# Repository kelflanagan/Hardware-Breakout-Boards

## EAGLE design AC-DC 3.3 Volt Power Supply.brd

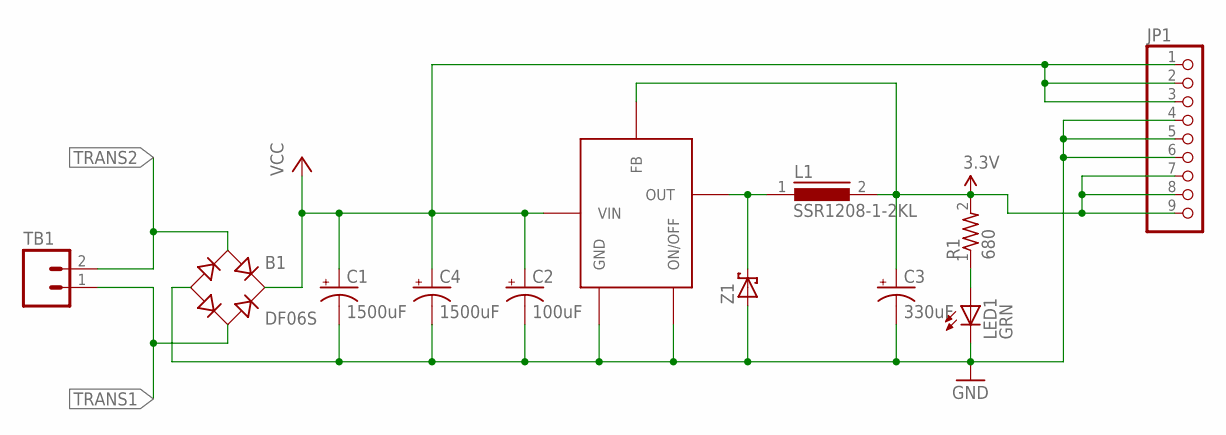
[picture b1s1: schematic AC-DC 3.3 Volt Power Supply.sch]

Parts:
B1: DF06S; DFS
C1, C4: 1500uF; CAP_J16
C2: 100uF; CAP_F
C3: 330uF; CAP_F
JP1: PINHD-1X9; 1X09
L1: SSR1208-1-2KL; DR125
LED1: GRN; CHIP-LED0603
R1: 680; 0603_RESISTOR
REG1: TL2575; TO-263-6
TB1: TERMINAL_BLOCK_2; TERMINL_BLOCK_2_POS
Z1: SCHOTTKY_DIODE; DIODE_SMB

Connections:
3.3V: C3.+, JP1.7, JP1.8, JP1.9, L1.2, R1.2, REG1.4 (FB)
GND: B1.-, C1.1 (-), C2.-, C3.-, C4.1 (-), JP1.4, JP1.5, JP1.6, LED1.C, REG1.3 (GND), REG1.5 (ON/OFF), Z1.A
unnamed: LED1.A, R1.1
unnamed: L1.1, REG1.2 (OUT), Z1.C
TRANS1: B1.AC2, TB1.1
TRANS2: B1.AC1, TB1.2
VCC: B1.+, C1.2 (+), C2.+, C4.2 (+), JP1.1, JP1.2, JP1.3, REG1.1 (VIN)

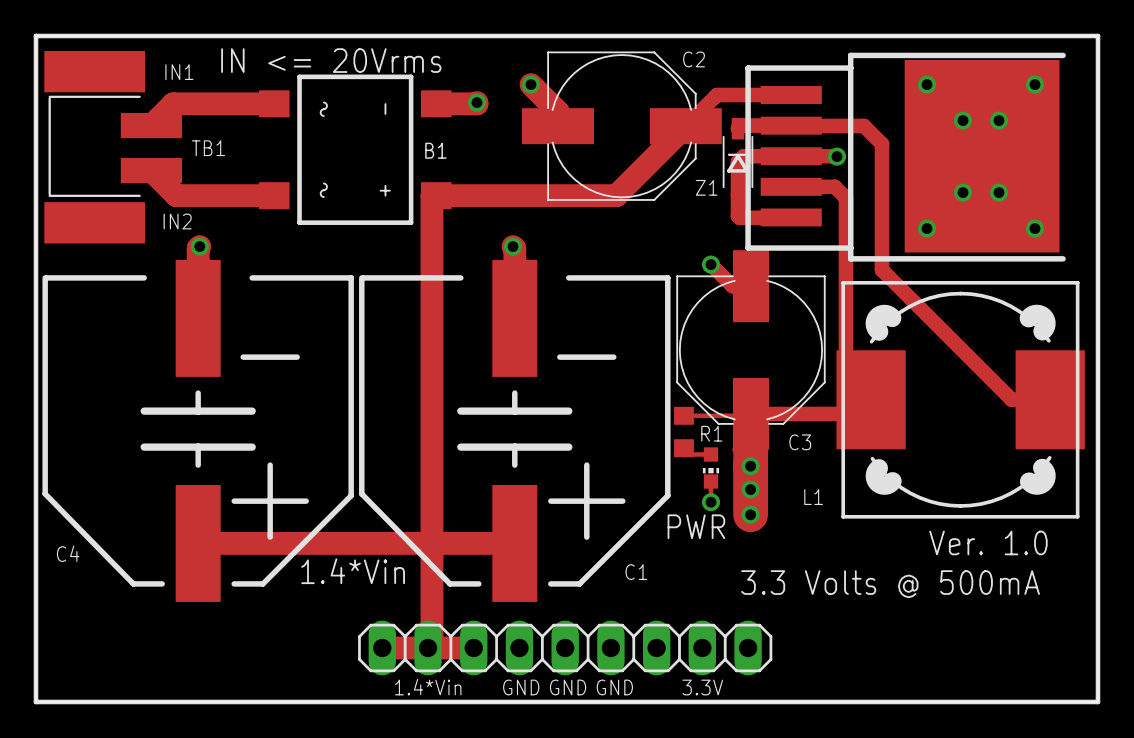
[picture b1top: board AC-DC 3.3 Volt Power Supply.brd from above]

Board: 4 copper layers, 59.0 x 37.0 mm, 12 parts (0 on the bottom side), 7 nets.

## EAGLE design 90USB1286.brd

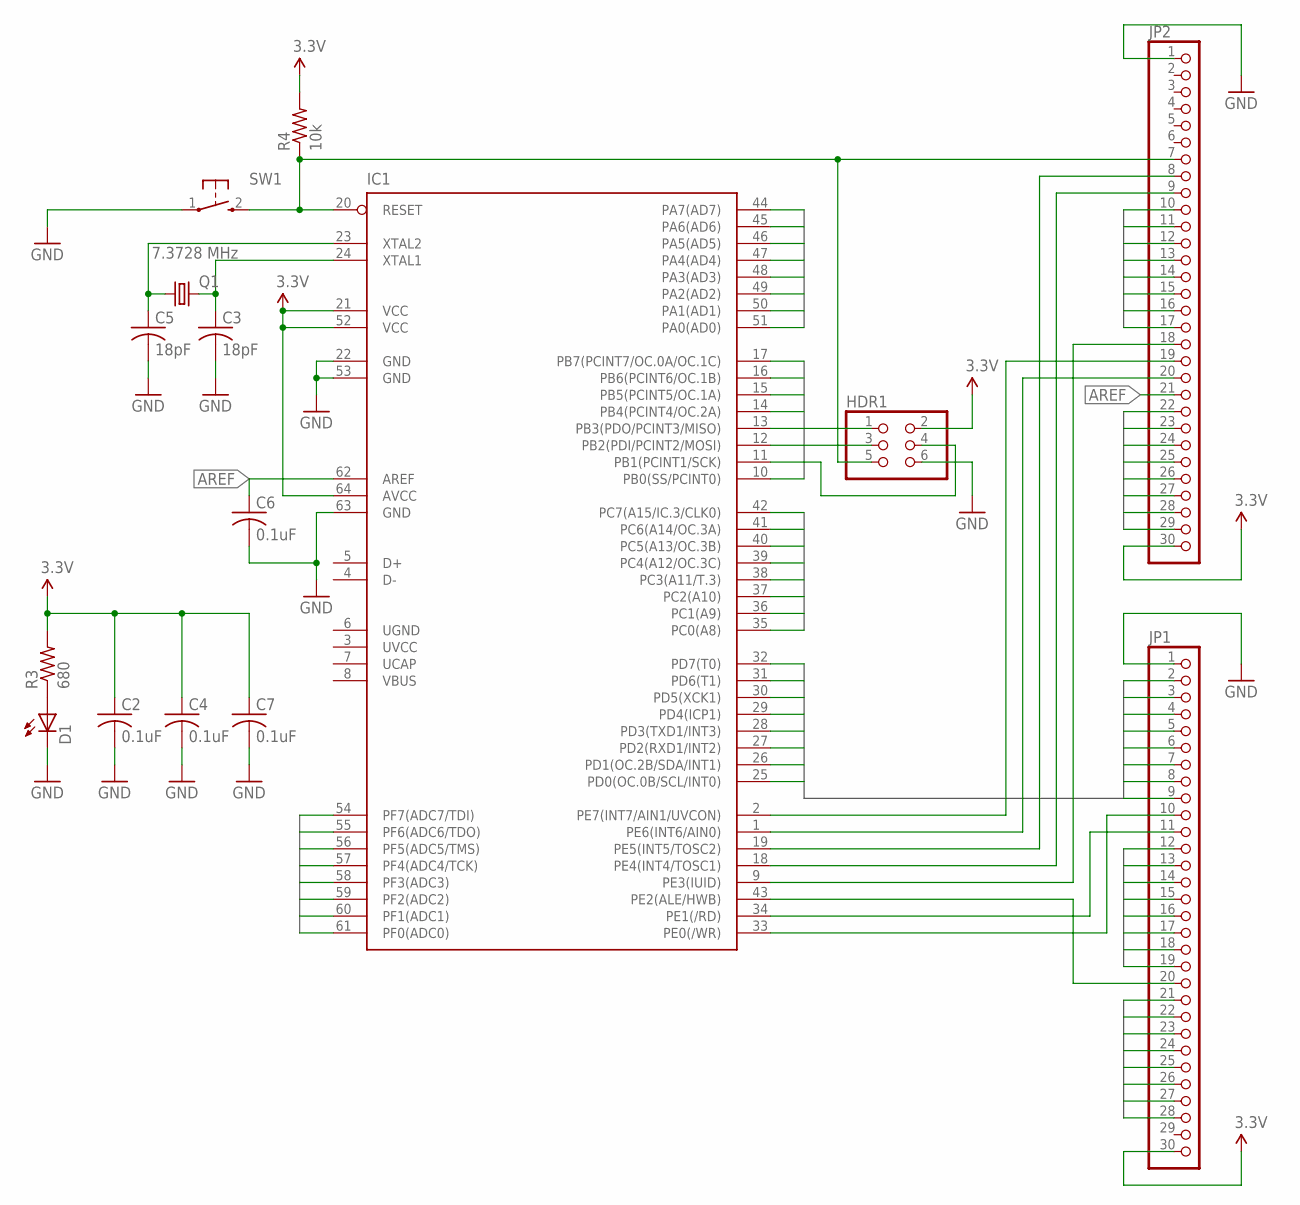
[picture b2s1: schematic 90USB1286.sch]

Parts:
C2, C4, C6, C7: 0.1uF; 0603_RESISTOR
C3, C5: 18pF; 0603_RESISTOR
D1: LEDCHIP-LED0603; CHIP-LED0603
HDR1: HEADER_2X3
IC1: AT90USB1286MLF; MLF64
JP1, JP2: PINHD-1X30; 1X30
Q1: 7.3728 MHz; CTS406
R3: 680; 0603_RESISTOR
R4: 10k; 0603_RESISTOR
SW1: TAC-SWITCH

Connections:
3.3V: C2.1, C4.1, C7.1, HDR1.2, IC1.21 (VCC), IC1.52 (VCC), IC1.64 (AVCC), JP1.30, JP2.30, R3.2, R4.2
A0: IC1.51 (PA0(AD0)), JP1.28
A1: IC1.50 (PA1(AD1)), JP1.27
A2: IC1.49 (PA2(AD2)), JP1.26
A3: IC1.48 (PA3(AD3)), JP1.25
A4: IC1.47 (PA4(AD4)), JP1.24
A5: IC1.46 (PA5(AD5)), JP1.23
A6: IC1.45 (PA6(AD6)), JP1.22
A7: IC1.44 (PA7(AD7)), JP1.21
AREF: C6.1, IC1.62 (AREF), JP2.21
B0: IC1.10 (PB0(SS/PCINT0)), JP2.17
B1: HDR1.3, IC1.11 (PB1(PCINT1/SCK)), JP2.16
B2: HDR1.4, IC1.12 (PB2(PDI/PCINT2/MOSI)), JP2.15
B3: HDR1.1, IC1.13 (PB3(PDO/PCINT3/MISO)), JP2.14
B4: IC1.14 (PB4(PCINT4/OC.2A)), JP2.13
B5: IC1.15 (PB5(PCINT5/OC.1A)), JP2.12
B6: IC1.16 (PB6(PCINT6/OC.1B)), JP2.11
B7: IC1.17 (PB7(PCINT7/OC.0A/OC.1C)), JP2.10
C0: IC1.35 (PC0(A8)), JP1.12
C1: IC1.36 (PC1(A9)), JP1.13
C2: IC1.37 (PC2(A10)), JP1.14
C3: IC1.38 (PC3(A11/T.3)), JP1.15
C4: IC1.39 (PC4(A12/OC.3C)), JP1.16
C5: IC1.40 (PC5(A13/OC.3B)), JP1.17
C6: IC1.41 (PC6(A14/OC.3A)), JP1.18
C7: IC1.42 (PC7(A15/IC.3/CLK0)), JP1.19
D0: IC1.25 (PD0(OC.0B/SCL/INT0)), JP1.2
D1: IC1.26 (PD1(OC.2B/SDA/INT1)), JP1.3
D2: IC1.27 (PD2(RXD1/INT2)), JP1.4
D3: IC1.28 (PD3(TXD1/INT3)), JP1.5
D4: IC1.29 (PD4(ICP1)), JP1.6
D5: IC1.30 (PD5(XCK1)), JP1.7
D6: IC1.31 (PD6(T1)), JP1.8
D7: IC1.32 (PD7(T0)), JP1.9
E0: IC1.33 (PE0(/WR)), JP1.10
E1: IC1.34 (PE1(/RD)), JP1.11
E2: IC1.43 (PE2(ALE/HWB)), JP1.20
E3: IC1.9 (PE3(IUID)), JP2.18
E4: IC1.18 (PE4(INT4/TOSC1)), JP2.9
E5: IC1.19 (PE5(INT5/TOSC2)), JP2.8
E6: IC1.1 (PE6(INT6/AIN0)), JP2.20
E7: IC1.2 (PE7(INT7/AIN1/UVCON)), JP2.19
F0: IC1.61 (PF0(ADC0)), JP2.22
F1: IC1.60 (PF1(ADC1)), JP2.23
F2: IC1.59 (PF2(ADC2)), JP2.24
F3: IC1.58 (PF3(ADC3)), JP2.25
F4: IC1.57 (PF4(ADC4/TCK)), JP2.26
F5: IC1.56 (PF5(ADC5/TMS)), JP2.27
F6: IC1.55 (PF6(ADC6/TDO)), JP2.28
F7: IC1.54 (PF7(ADC7/TDI)), JP2.29
GND: C2.2, C3.2, C4.2, C5.2, C6.2, C7.2, D1.C, HDR1.6, IC1.22 (GND), IC1.53 (GND), IC1.63 (GND), JP1.1, JP2.1, SW1.1
unnamed: C5.1, IC1.23 (XTAL2), Q1.1
unnamed: C3.1, IC1.24 (XTAL1), Q1.3 (2)
unnamed: D1.A, R3.1
RESET: HDR1.5, IC1.20 (RESET), JP2.7, R4.1, SW1.2
UCAP: IC1.7 (UCAP)
UGND: IC1.6 (UGND)
UVCC: IC1.3 (UVCC)
VBUS: IC1.8 (VBUS)

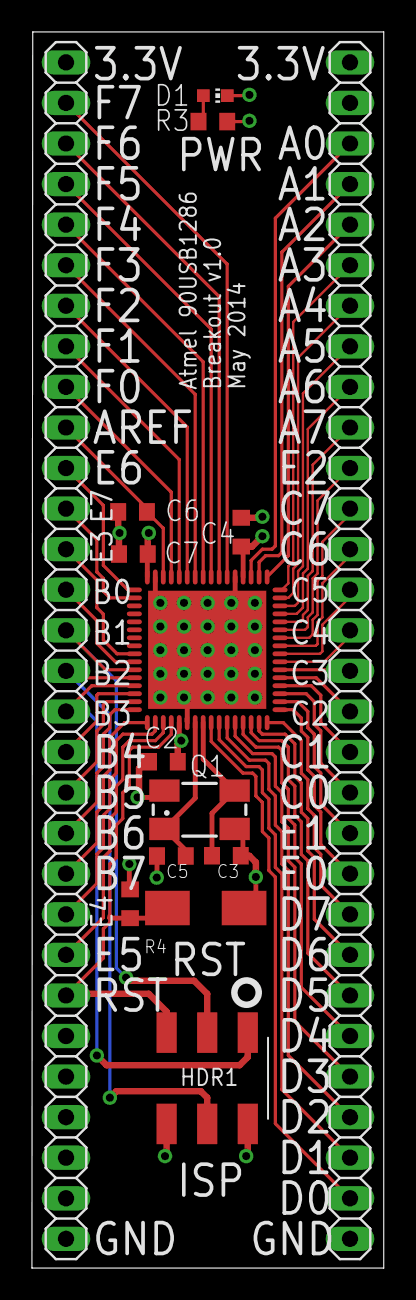
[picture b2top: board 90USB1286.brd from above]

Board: 4 copper layers, 22.0 x 77.4 mm, 15 parts (0 on the bottom side), 55 nets.

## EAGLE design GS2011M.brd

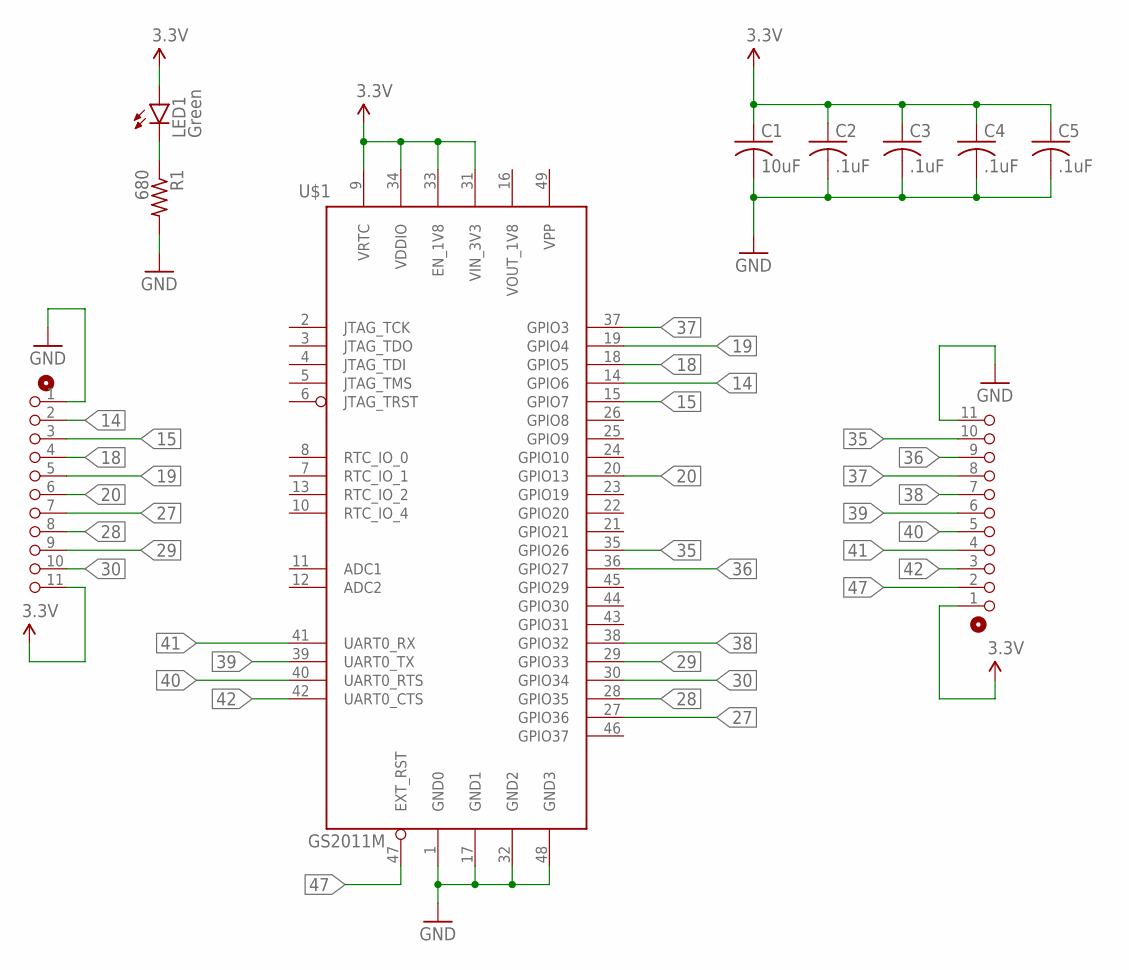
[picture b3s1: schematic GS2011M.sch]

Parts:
C1: 10uF; 0603_CAP
C2, C3, C4, C5: .1uF; 0603_CAP
LED1: Green; 0603_LED
P1, P2: PIN-11X1
R1: 680; 0603_RESISTOR
U$1: GS2011M

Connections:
3.3V: C1.1, C2.1, C3.1, C4.1, C5.1, LED1.A, P1.11, P2.1, U$1.9 (VRTC), U$1.31 (VIN_3V3), U$1.33 (EN_1V8), U$1.34 (VDDIO)
14: P1.2, U$1.14 (GPIO6)
15: P1.3, U$1.15 (GPIO7)
18: P1.4, U$1.18 (GPIO5)
19: P1.5, U$1.19 (GPIO4)
20: P1.6, U$1.20 (GPIO13)
27: P1.7, U$1.27 (GPIO36)
28: P1.8, U$1.28 (GPIO35)
29: P1.9, U$1.29 (GPIO33)
30: P1.10, U$1.30 (GPIO34)
35: P2.10, U$1.35 (GPIO26)
36: P2.9, U$1.36 (GPIO27)
37: P2.8, U$1.37 (GPIO3)
38: P2.7, U$1.38 (GPIO32)
39: P2.6, U$1.39 (UART0_TX)
40: P2.5, U$1.40 (UART0_RTS)
41: P2.4, U$1.41 (UART0_RX)
42: P2.3, U$1.42 (UART0_CTS)
47: P2.2, U$1.47 (EXT_RST)
GND: C1.2, C2.2, C3.2, C4.2, C5.2, P1.1, P2.11, R1.2, U$1.1 (GND0), U$1.17 (GND1), U$1.32 (GND2), U$1.48 (GND3)
unnamed: LED1.C, R1.1
VOUT_1V8: U$1.16 (VOUT_1V8)

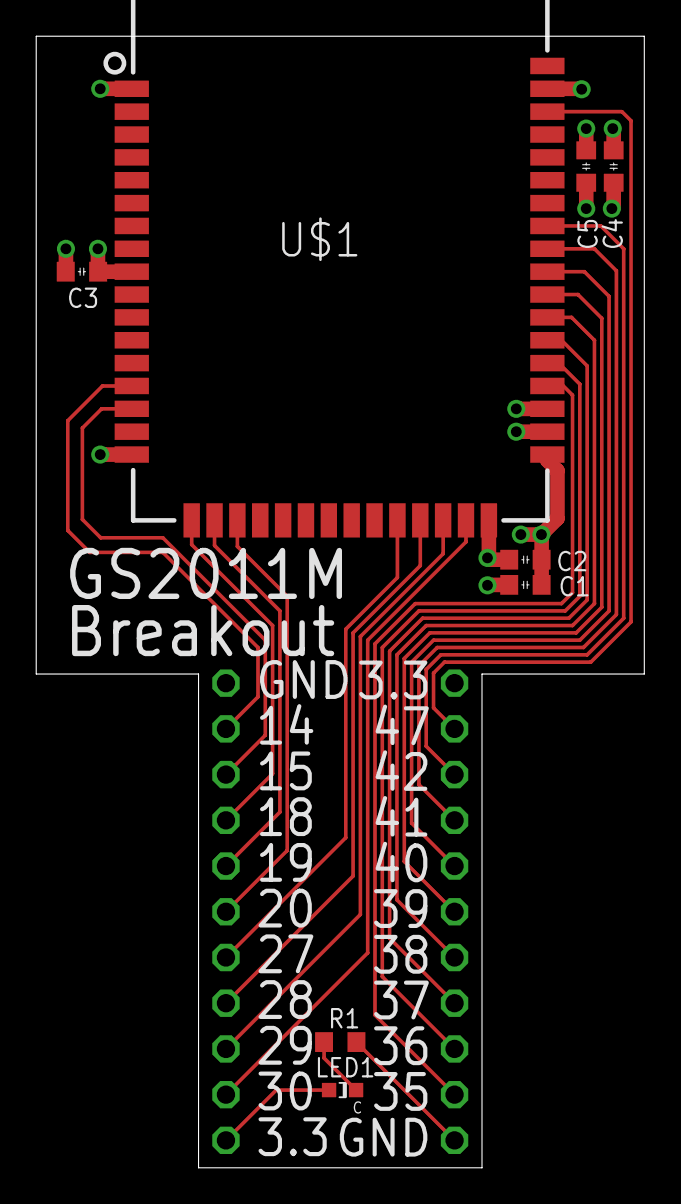
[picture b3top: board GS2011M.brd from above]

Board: 4 copper layers, 33.8 x 62.9 mm, 10 parts (0 on the bottom side), 21 nets.

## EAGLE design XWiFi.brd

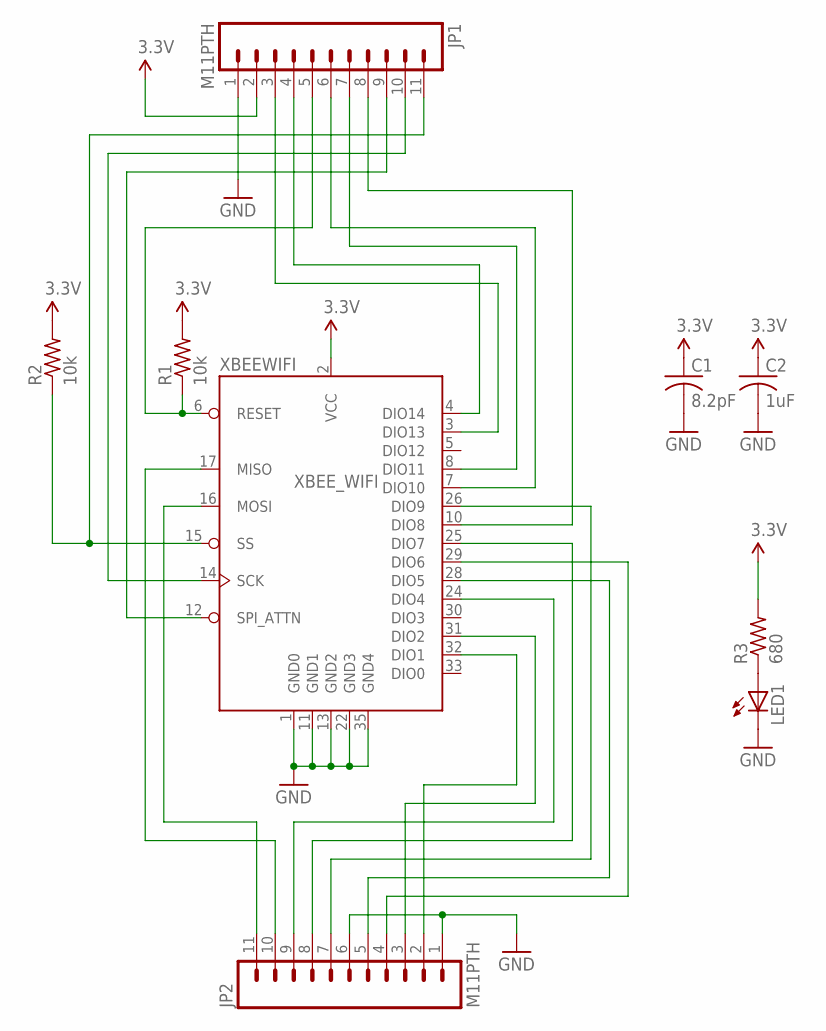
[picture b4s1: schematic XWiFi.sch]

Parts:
C1: 8.2pF; 0603_RESISTOR
C2: 1uF; 0603_RESISTOR
JP1, JP2: M11PTH; 1X11
LED1: LEDCHIP-LED0603; CHIP-LED0603
R1, R2: 10k; 0603_RESISTOR
R3: 680; 0603_RESISTOR
XBEEWIFI: XBEE_WIFI

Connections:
3.3V: C1.1, C2.1, JP1.2, R1.2, R2.2, R3.2, XBEEWIFI.2 (VCC)
GND: C1.2, C2.2, JP1.1, JP2.1, JP2.6, LED1.C, XBEEWIFI.1 (GND0), XBEEWIFI.11 (GND1), XBEEWIFI.13 (GND2), XBEEWIFI.22 (GND3), XBEEWIFI.35 (GND4)
unnamed: JP1.5, R1.1, XBEEWIFI.6 (RESET)
unnamed: JP1.11, R2.1, XBEEWIFI.15 (SS)
unnamed: LED1.A, R3.1
unnamed: JP1.3, XBEEWIFI.3 (DIO13)
unnamed: JP1.4, XBEEWIFI.4 (DIO14)
unnamed: JP1.6, XBEEWIFI.7 (DIO10)
unnamed: JP1.7, XBEEWIFI.8 (DIO11)
unnamed: JP2.9, XBEEWIFI.24 (DIO4)
unnamed: JP1.8, XBEEWIFI.10 (DIO8)
unnamed: JP1.9, XBEEWIFI.12 (SPI_ATTN)
unnamed: JP1.10, XBEEWIFI.14 (SCK)
unnamed: JP2.11, XBEEWIFI.16 (MOSI)
unnamed: JP2.3, XBEEWIFI.31 (DIO2)
unnamed: JP2.2, XBEEWIFI.32 (DIO1)
unnamed: JP2.8, XBEEWIFI.25 (DIO7)
unnamed: JP2.7, XBEEWIFI.26 (DIO9)
unnamed: JP2.5, XBEEWIFI.28 (DIO5)
unnamed: JP2.4, XBEEWIFI.29 (DIO6)
unnamed: JP2.10, XBEEWIFI.17 (MISO)

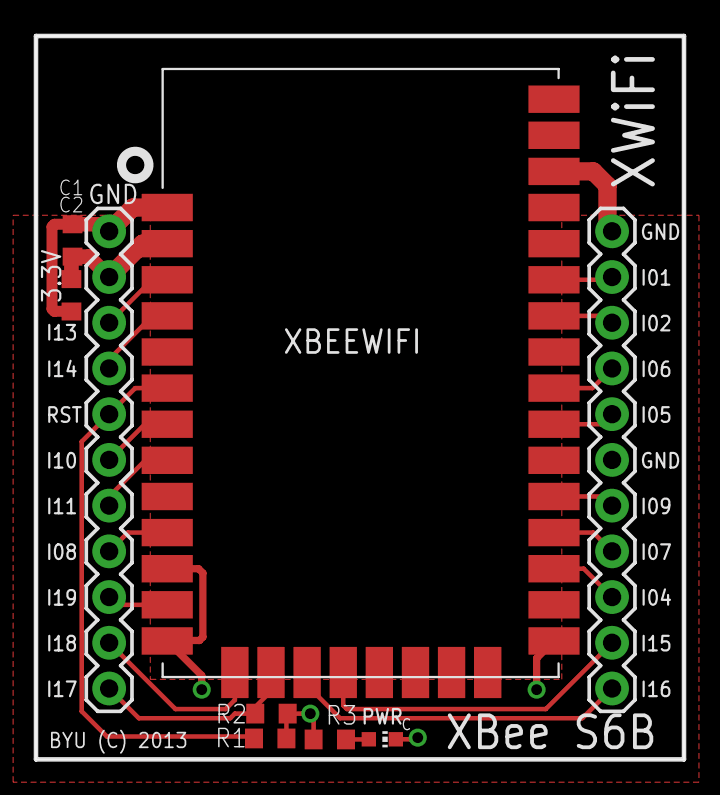
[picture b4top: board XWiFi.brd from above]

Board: 4 copper layers, 36.0 x 40.2 mm, 9 parts (0 on the bottom side), 21 nets.

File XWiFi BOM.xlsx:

Part | Value | Device
C1 | 8.2pF | 0603 Cap
C2 | 1 uF | 0603 Cap
R1 | 10k Ohm | 0603 Resistor
R2 | 10k Ohm | 0603 Resistor
R3 | 680 Ohm | 0603 Resistor
LED1 | Green LED | 0603 LED
Xbee1 | Xbee Wifi Module | Module
HDR1 | 11 pin header | 1x11 header
HDR2 | 11 pin header | 1x11 header

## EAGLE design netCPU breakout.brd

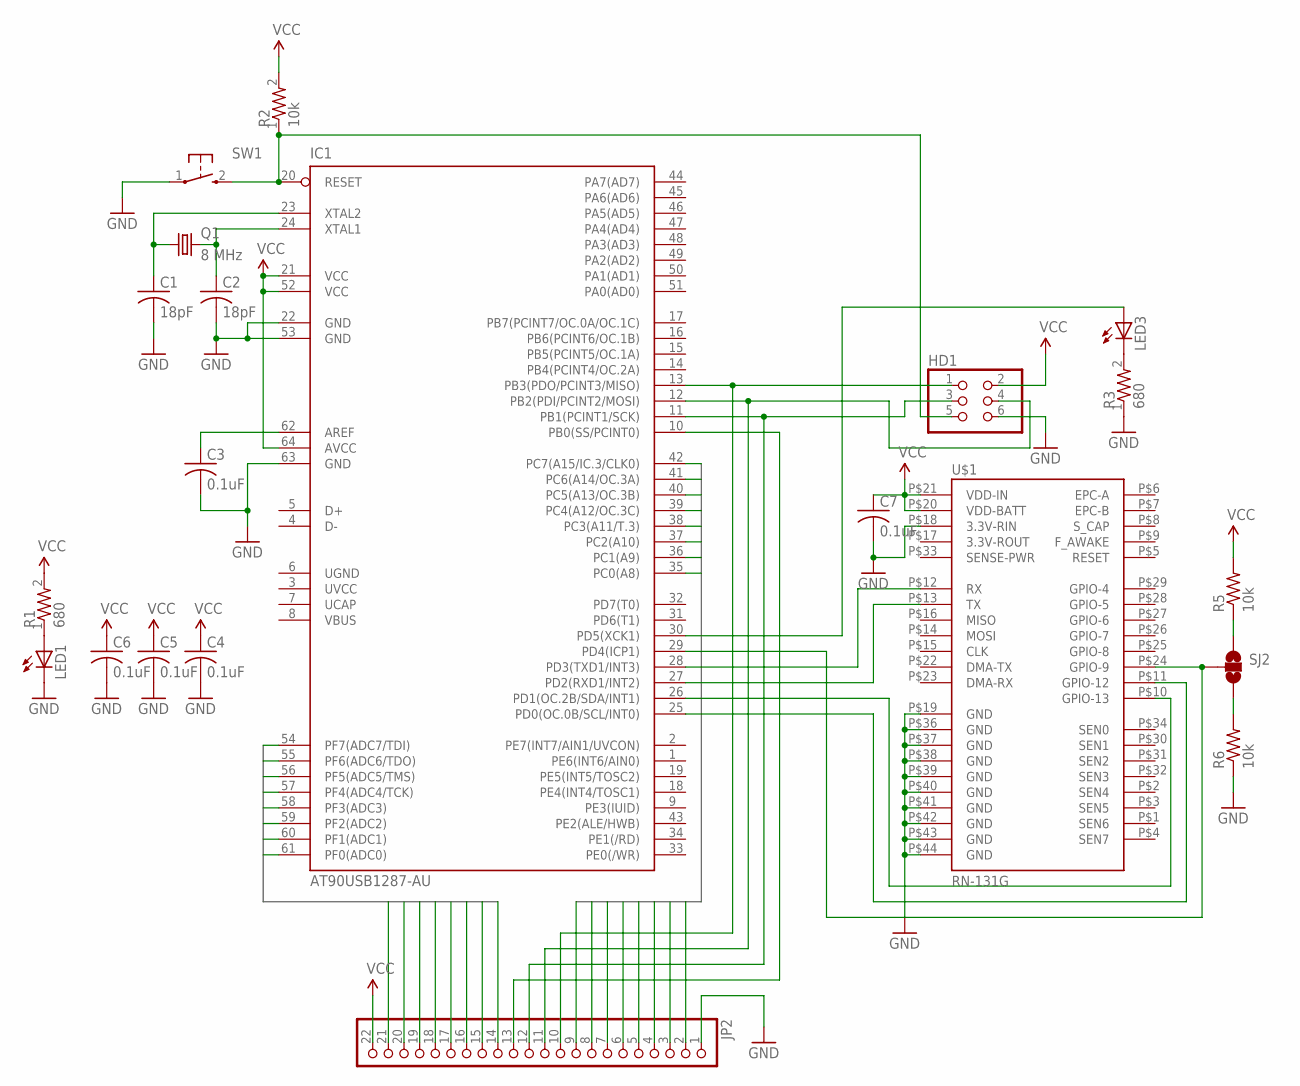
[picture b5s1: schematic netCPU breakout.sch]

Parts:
C1, C2: 18pF; C0603K
C3, C4, C5, C6, C7: 0.1uF; C0603K
HD1: HEADER2X3
IC1: AT90USB1287-AU; TQFP64
JP2: PINHD-1X22; 1X22
LED1, LED3: LEDCHIP-LED0603; CHIP-LED0603
Q1: 8 MHz; HC49UP
R1, R3: 680; 0603_RESISTOR
R2: 10k; 0603_RESISTOR
R5, R6: 10k; R0603
SJ2: SOLDERJUMPER_2WAYPASTE2&3; SJ_3_PASTE2&3
SW1: TAC-SWITCH
U$1: RN-131G

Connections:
GND: C1.2, C2.2, C3.2, C4.2, C5.2, C6.2, C7.2, HD1.6, IC1.22 (GND), IC1.53 (GND), IC1.63 (GND), JP2.1, LED1.C, R3.1, R6.1, SW1.1, U$1.P$18 (3.3V-RIN), U$1.P$19 (GND), U$1.P$36 (GND), U$1.P$37 (GND), U$1.P$38 (GND), U$1.P$39 (GND), U$1.P$40 (GND), U$1.P$41 (GND), U$1.P$42 (GND), U$1.P$43 (GND), U$1.P$44 (GND)
MISO: HD1.1, IC1.13 (PB3(PDO/PCINT3/MISO)), JP2.10
MOSI: HD1.4, IC1.12 (PB2(PDI/PCINT2/MOSI)), JP2.11
unnamed: C1.1, IC1.23 (XTAL2), Q1.1
unnamed: C2.1, IC1.24 (XTAL1), Q1.2
unnamed: LED1.A, R1.1
unnamed: LED3.C, R3.2
unnamed: IC1.28 (PD3(TXD1/INT3)), U$1.P$12 (RX)
unnamed: C3.1, IC1.62 (AREF)
unnamed: IC1.27 (PD2(RXD1/INT2)), U$1.P$13 (TX)
unnamed: IC1.26 (PD1(OC.2B/SDA/INT1)), U$1.P$10 (GPIO-13)
unnamed: IC1.25 (PD0(OC.0B/SCL/INT0)), U$1.P$11 (GPIO-12)
unnamed: IC1.29 (PD4(ICP1)), SJ2.2, U$1.P$24 (GPIO-9)
unnamed: IC1.30 (PD5(XCK1)), LED3.A
unnamed: R6.2, SJ2.3
unnamed: R5.1, SJ2.1
PC0: IC1.35 (PC0(A8)), JP2.2
PC1: IC1.36 (PC1(A9)), JP2.3
PC2: IC1.37 (PC2(A10)), JP2.4
PC3: IC1.38 (PC3(A11/T.3)), JP2.5
PC4: IC1.39 (PC4(A12/OC.3C)), JP2.6
PC5: IC1.40 (PC5(A13/OC.3B)), JP2.7
PC6: IC1.41 (PC6(A14/OC.3A)), JP2.8
PC7: IC1.42 (PC7(A15/IC.3/CLK0)), JP2.9
PF0: IC1.61 (PF0(ADC0)), JP2.14
PF1: IC1.60 (PF1(ADC1)), JP2.15
PF2: IC1.59 (PF2(ADC2)), JP2.16
PF3: IC1.58 (PF3(ADC3)), JP2.17
PF4: IC1.57 (PF4(ADC4/TCK)), JP2.18
PF5: IC1.56 (PF5(ADC5/TMS)), JP2.19
PF6: IC1.55 (PF6(ADC6/TDO)), JP2.20
PF7: IC1.54 (PF7(ADC7/TDI)), JP2.21
RESET: HD1.5, IC1.20 (RESET), R2.1, SW1.2
SCK: HD1.3, IC1.11 (PB1(PCINT1/SCK)), JP2.12
SS: IC1.10 (PB0(SS/PCINT0)), JP2.13
UCAP: IC1.7 (UCAP)
UGND: IC1.6 (UGND)
UVCC: IC1.3 (UVCC)
VBUS: IC1.8 (VBUS)
VCC: C4.1, C5.1, C6.1, C7.1, HD1.2, IC1.21 (VCC), IC1.52 (VCC), IC1.64 (AVCC), JP2.22, R1.2, R2.2, R5.2, U$1.P$20 (VDD-BATT), U$1.P$21 (VDD-IN)

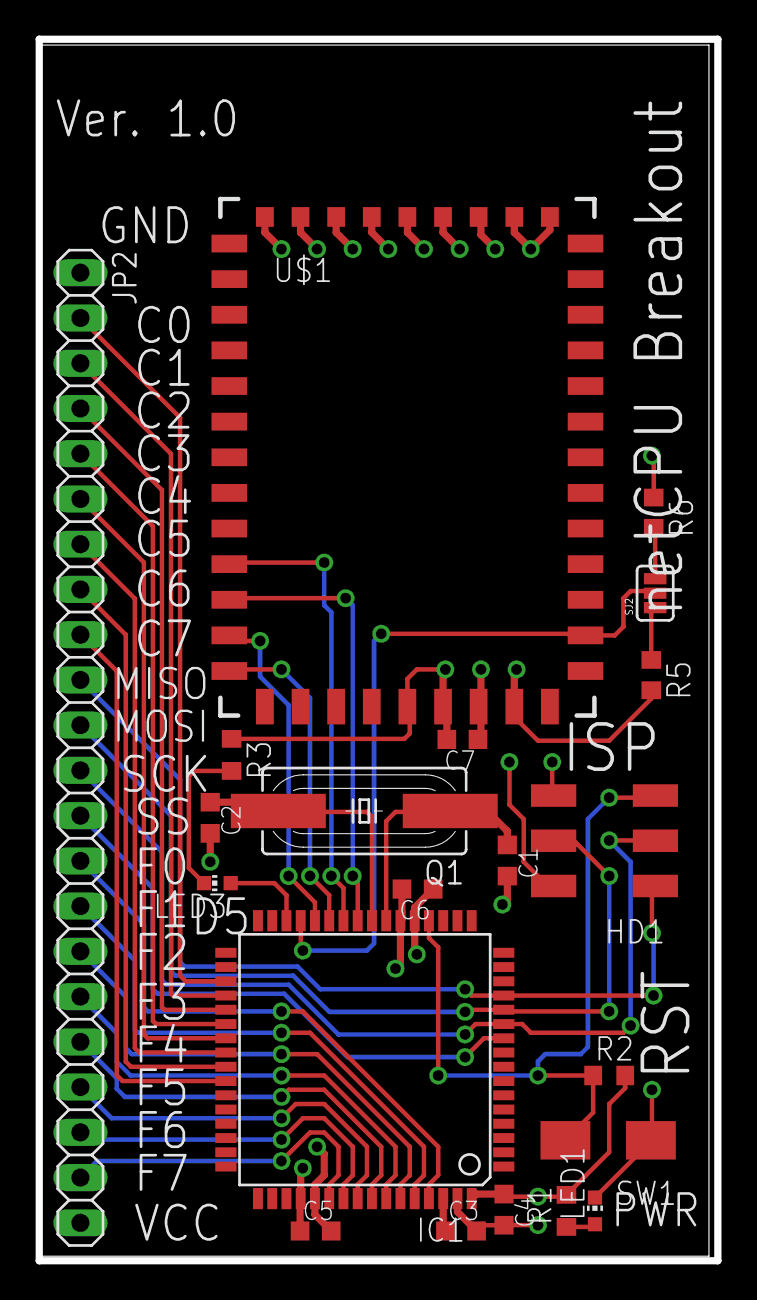
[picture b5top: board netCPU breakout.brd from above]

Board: 4 copper layers, 38.1 x 68.6 mm, 21 parts (0 on the bottom side), 36 nets.

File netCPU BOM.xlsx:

Designation | Description | Size / Value | DigiKey PN | Manufacturer | Unit Price @100 | Reeling Cost | Unit Price
HD1 | Header | 2x3 | 609-3487-6-ND |  | 0.90100000000000002 | 7 | 1.1000000000000001
R1 | Resistor | 680 | P680GDKR-ND | Panasonic | 7.6999999999999999E-2 | 7 | 0.1
R2 | Resistor | 10k | P10KGDKR-ND | Panasonic | 7.6999999999999999E-2 | 7 | 0.1
R3 | Resistor | 680 | P680GDKR-ND | Panasonic | 7.6999999999999999E-2 | 7 | 0.1
R4 | Resistor | 10k | P10KGDKR-ND | Panasonic | 7.6999999999999999E-2 | 7 | 0.1
C1 | Capacitor | 18pF | 399-1052-6-ND | Kemet | 8.5400000000000004E-2 | 7 | 0.1
C2 | Capacitor | 18pF | 399-1052-6-ND | Kemet | 8.5400000000000004E-2 | 7 | 0.1
C3 | Capacitor | 0.1uF | 399-1096-6-ND | Kemet | 7.9899999999999999E-2 | 7 | 0.1
C4 | Capacitor | 0.1uF | 399-1096-6-ND | Kemet | 7.9899999999999999E-2 | 7 | 0.1
C5 | Capacitor | 0.1uF | 399-1096-6-ND | Kemet | 7.9899999999999999E-2 | 7 | 0.1
C6 | Capacitor | 0.1uF | 399-1096-6-ND | Kemet | 7.9899999999999999E-2 | 7 | 0.1
C7 | Capacitor | 0.1uF | 399-1096-6-ND | Kemet | 7.9899999999999999E-2 | 7 | 0.1
Q1 | Crystal | 8MHz | 535-10212-6-ND | ABLS | 0.3175 | 7 | 0.41
SW1 | Tactile Switch | NA | EG4576DKR-ND | E-Switch | 0.62880000000000003 | 7 | 0.77
IC1 | AT90USB1286 | 64TQFP | AT90USB1286-AURCT-ND | Atmel | 10.83 | 0 | 10.83
IC2 | RN-131C | 44 pin Module | 740-1036-ND | MicroChip | 32.39 | 0 | 34.950000000000003
LED1 | Green LED | 0603 | 516-2493-6-ND | Avago | 0.28199999999999997 | 7 | 0.54
LED2 | Green LED | 0603 | 516-2493-6-ND | Avago | 0.28199999999999997 | 7 | 0.54
JP2 | Header | 22x1 | 929400E-01-36-ND | 3M | 0.96799999999999997 |  | 1.28

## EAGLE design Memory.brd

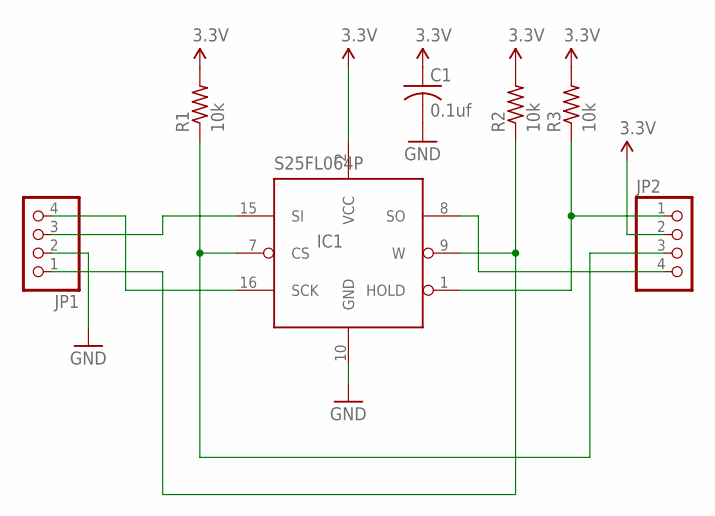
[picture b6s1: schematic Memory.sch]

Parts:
C1: 0.1uf; 0603_CAP
IC1: S25FL064P; SOIC-16
JP1, JP2: PINHD-1X4; 1X04
R1, R2, R3: 10k; 0603_RESISTOR

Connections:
3.3V: C1.1, IC1.2 (VCC), JP2.2, R1.2, R2.2, R3.2
GND: C1.2, IC1.10 (GND), JP1.2
unnamed: IC1.7 (CS), JP2.3, R1.1
unnamed: IC1.9 (W), JP1.1, R2.1
unnamed: IC1.1 (HOLD), JP2.1, R3.1
unnamed: IC1.8 (SO), JP2.4
unnamed: IC1.15 (SI), JP1.3
unnamed: IC1.16 (SCK), JP1.4

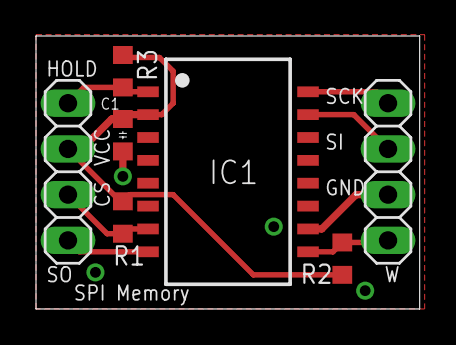
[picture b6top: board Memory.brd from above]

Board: 2 copper layers, 21.3 x 15.2 mm, 7 parts (0 on the bottom side), 8 nets.

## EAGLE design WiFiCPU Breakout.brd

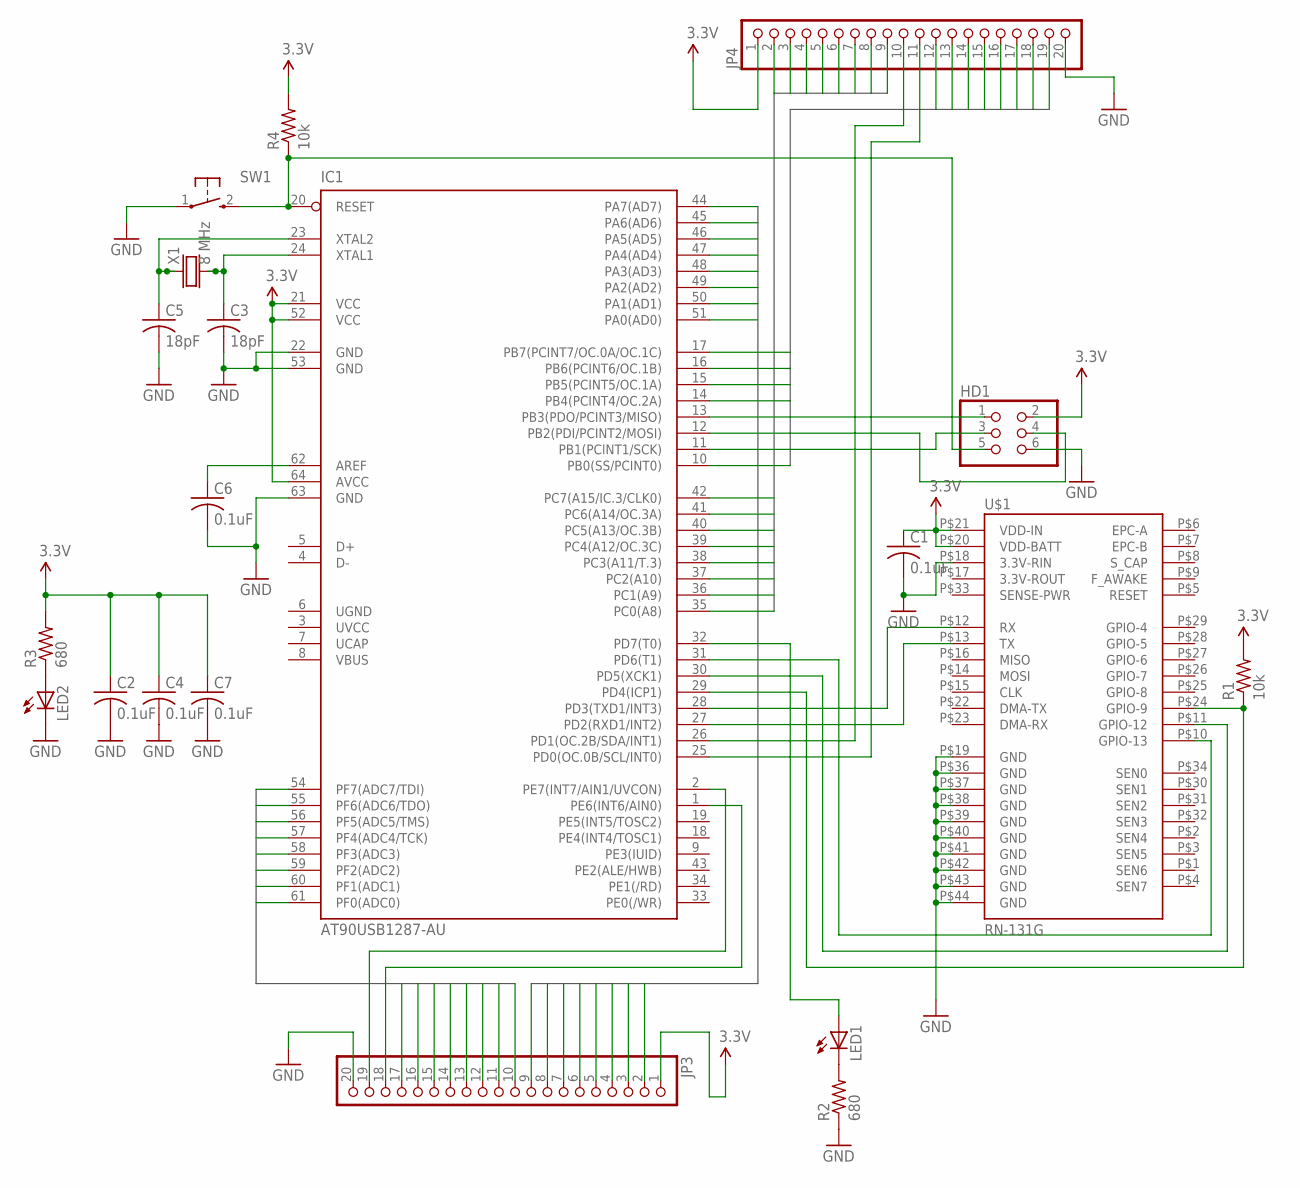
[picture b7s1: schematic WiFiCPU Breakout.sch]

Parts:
C1, C2, C4, C6, C7: 0.1uF; 0603_RESISTOR
C3, C5: 18pF; 0603_RESISTOR
HD1: HEADER2X3
IC1: AT90USB1287-AU; TQFP64
JP3, JP4: PINHD-1X20; 1X20
LED1, LED2: LEDCHIP-LED0603; CHIP-LED0603
R1, R4: 10k; 0603_RESISTOR
R2, R3: 680; 0603_RESISTOR
SW1: TAC-SWITCH
U$1: RN-131G
X1: 8 MHz; CRYSTAL_5X3

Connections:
3.3V: C1.1, C2.1, C4.1, C7.1, HD1.2, IC1.21 (VCC), IC1.52 (VCC), IC1.64 (AVCC), JP3.1, JP4.1, R1.2, R3.2, R4.2, U$1.P$20 (VDD-BATT), U$1.P$21 (VDD-IN)
GND: C1.2, C2.2, C3.2, C4.2, C5.2, C6.2, C7.2, HD1.6, IC1.22 (GND), IC1.53 (GND), IC1.63 (GND), JP3.20, JP4.20, LED2.C, R2.1, SW1.1, U$1.P$18 (3.3V-RIN), U$1.P$19 (GND), U$1.P$36 (GND), U$1.P$37 (GND), U$1.P$38 (GND), U$1.P$39 (GND), U$1.P$40 (GND), U$1.P$41 (GND), U$1.P$42 (GND), U$1.P$43 (GND), U$1.P$44 (GND)
unnamed: C5.1, IC1.23 (XTAL2), X1.1
unnamed: C3.1, IC1.24 (XTAL1), X1.2
unnamed: LED2.A, R3.1
unnamed: LED1.C, R2.2
unnamed: IC1.32 (PD7(T0)), LED1.A
unnamed: IC1.28 (PD3(TXD1/INT3)), U$1.P$12 (RX)
unnamed: C6.1, IC1.62 (AREF)
unnamed: IC1.27 (PD2(RXD1/INT2)), U$1.P$13 (TX)
unnamed: IC1.31 (PD6(T1)), U$1.P$10 (GPIO-13)
unnamed: IC1.30 (PD5(XCK1)), U$1.P$11 (GPIO-12)
unnamed: IC1.29 (PD4(ICP1)), R1.1, U$1.P$24 (GPIO-9)
PA0: IC1.51 (PA0(AD0)), JP3.9
PA1: IC1.50 (PA1(AD1)), JP3.8
PA2: IC1.49 (PA2(AD2)), JP3.7
PA3: IC1.48 (PA3(AD3)), JP3.6
PA4: IC1.47 (PA4(AD4)), JP3.5
PA5: IC1.46 (PA5(AD5)), JP3.4
PA6: IC1.45 (PA6(AD6)), JP3.3
PA7: IC1.44 (PA7(AD7)), JP3.2
PB0: IC1.10 (PB0(SS/PCINT0)), JP4.19
PB1: HD1.3, IC1.11 (PB1(PCINT1/SCK)), JP4.18
PB2: HD1.4, IC1.12 (PB2(PDI/PCINT2/MOSI)), JP4.17
PB3: HD1.1, IC1.13 (PB3(PDO/PCINT3/MISO)), JP4.16
PB4: IC1.14 (PB4(PCINT4/OC.2A)), JP4.15
PB5: IC1.15 (PB5(PCINT5/OC.1A)), JP4.14
PB6: IC1.16 (PB6(PCINT6/OC.1B)), JP4.13
PB7: IC1.17 (PB7(PCINT7/OC.0A/OC.1C)), JP4.12
PC0: IC1.35 (PC0(A8)), JP4.9
PC1: IC1.36 (PC1(A9)), JP4.8
PC2: IC1.37 (PC2(A10)), JP4.7
PC3: IC1.38 (PC3(A11/T.3)), JP4.6
PC4: IC1.39 (PC4(A12/OC.3C)), JP4.5
PC5: IC1.40 (PC5(A13/OC.3B)), JP4.4
PC6: IC1.41 (PC6(A14/OC.3A)), JP4.3
PC7: IC1.42 (PC7(A15/IC.3/CLK0)), JP4.2
PD0: IC1.25 (PD0(OC.0B/SCL/INT0)), JP4.11
PD1: IC1.26 (PD1(OC.2B/SDA/INT1)), JP4.10
PE6: IC1.1 (PE6(INT6/AIN0)), JP3.18
PE7: IC1.2 (PE7(INT7/AIN1/UVCON)), JP3.19
PF0: IC1.61 (PF0(ADC0)), JP3.17
PF1: IC1.60 (PF1(ADC1)), JP3.16
PF2: IC1.59 (PF2(ADC2)), JP3.15
PF3: IC1.58 (PF3(ADC3)), JP3.14
PF4: IC1.57 (PF4(ADC4/TCK)), JP3.13
PF5: IC1.56 (PF5(ADC5/TMS)), JP3.12
PF6: IC1.55 (PF6(ADC6/TDO)), JP3.11
PF7: IC1.54 (PF7(ADC7/TDI)), JP3.10
RESET: HD1.5, IC1.20 (RESET), R4.1, SW1.2
UCAP: IC1.7 (UCAP)
UGND: IC1.6 (UGND)
UVCC: IC1.3 (UVCC)
VBUS: IC1.8 (VBUS)

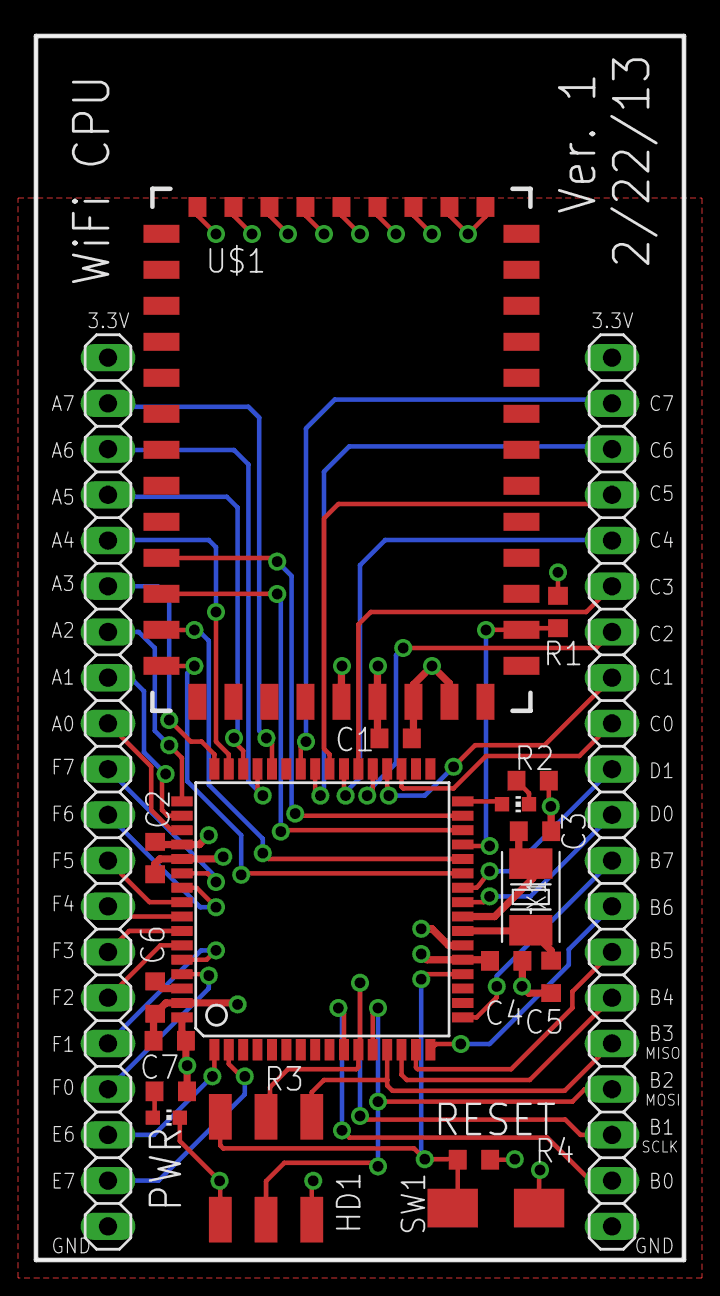
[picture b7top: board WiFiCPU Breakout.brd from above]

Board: 4 copper layers, 36.0 x 68.0 mm, 20 parts (0 on the bottom side), 50 nets.

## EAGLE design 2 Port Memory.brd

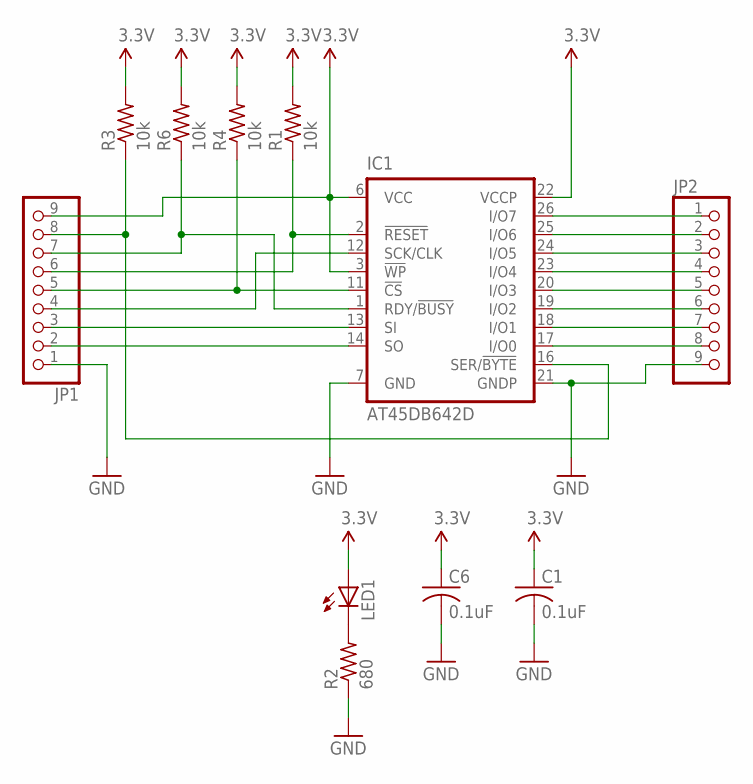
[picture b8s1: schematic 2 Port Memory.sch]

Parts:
C1, C6: 0.1uF; 0603_RESISTOR
IC1: AT45DB642D; 28T-TSOP-1
JP1, JP2: PINHD-1X9; 1X09
LED1: LEDCHIP-LED0603; CHIP-LED0603
R1, R3, R4, R6: 10k; 0603_RESISTOR
R2: 680; 0603_RESISTOR

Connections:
3.3V: C1.1, C6.1, IC1.3 (!WP), IC1.6 (VCC), IC1.22 (VCCP), JP1.9, LED1.A, R1.2, R3.2, R4.2, R6.2
GND: C1.2, C6.2, IC1.7 (GND), IC1.21 (GNDP), JP1.1, JP2.9, R2.1
unnamed: IC1.1 (RDY/!BUSY), JP1.7, R6.1
unnamed: IC1.11 (!CS), JP1.5, R4.1
unnamed: IC1.12 (SCK/CLK), JP1.4
unnamed: LED1.C, R2.2
unnamed: IC1.16 (SER/!BYTE), JP1.8, R3.1
unnamed: IC1.17 (I/O0), JP2.8
unnamed: IC1.18 (I/O1), JP2.7
unnamed: IC1.19 (I/O2), JP2.6
unnamed: IC1.20 (I/O3), JP2.5
unnamed: IC1.23 (I/O4), JP2.4
unnamed: IC1.24 (I/O5), JP2.3
unnamed: IC1.25 (I/O6), JP2.2
unnamed: IC1.26 (I/O7), JP2.1
unnamed: IC1.14 (SO), JP1.2
unnamed: IC1.13 (SI), JP1.3
unnamed: IC1.2 (!RESET), JP1.6, R1.1

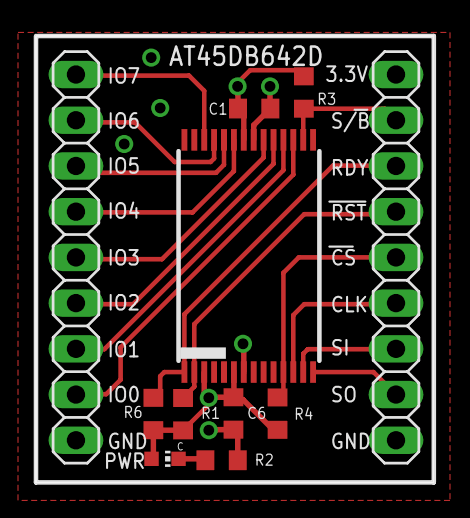
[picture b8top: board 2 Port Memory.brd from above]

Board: 4 copper layers, 22.1 x 24.8 mm, 11 parts (0 on the bottom side), 18 nets.

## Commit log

2016-05-04 Frist commit

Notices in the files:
XWiFi.brd:
BYU (C) 2013
parts and their libraries:
SparkFun-Aesthetics: Licensing: CC v3.0 Share-Alike You are welcome to use this library for commercial purposes.
